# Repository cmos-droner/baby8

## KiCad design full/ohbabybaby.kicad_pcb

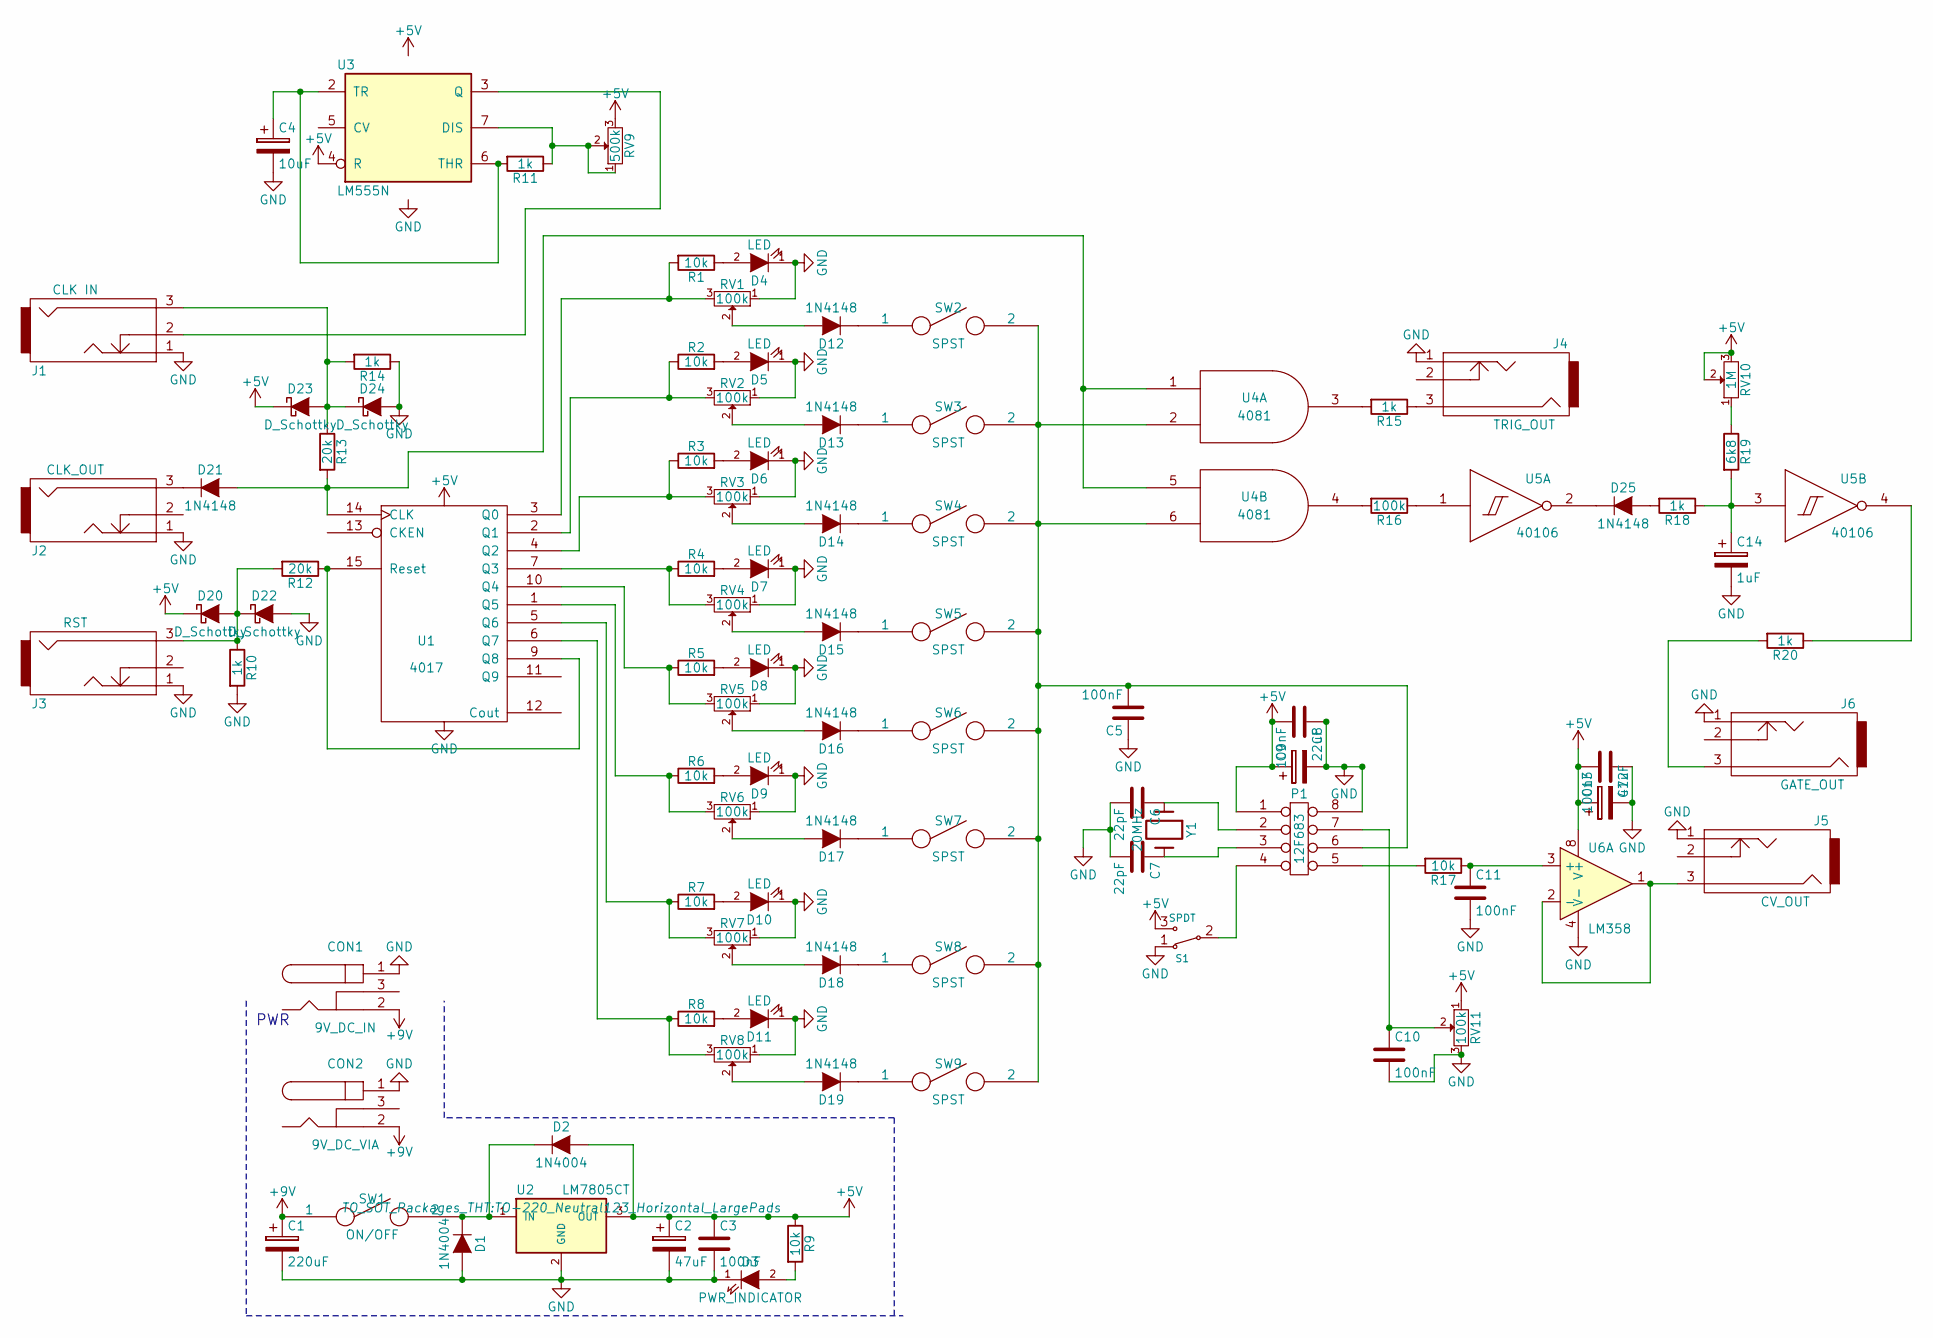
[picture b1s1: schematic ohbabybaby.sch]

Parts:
C1: 220uF; C_Radial_D8_L11.5_P3.5
C2, C13: 47uF; C_Radial_D7.5_L11.2_P2.5
C3, C5, C8, C10, C11, C12: 100nF; C_Rect_L7_W2.5_P5
C4: 10uF; C_Radial_D5_L11_P2.5
C6, C7: 22pF; C_Rect_L7_W2.5_P5
C9: 22uF; C_Radial_D5_L11_P2.5
C14: 1uF; C_Radial_D5_L11_P2.5
CON1: 9V_DC_IN; BARREL_JACK
CON2: 9V_DC_VIA; BARREL_JACK
D1, D2: 1N4004; Diode_DO-41_SOD81_Horizontal_RM10
D3: PWR_INDICATOR; LED-5MM-3
D4, D5, D6, D7, D8, D9, D10, D11: LED; LED-5MM-3
D12, D13, D14, D15, D16, D17, D18, D19, D21, D25: 1N4148; Diode_DO-35_SOD27_Horizontal_RM10
D20, D22, D23, D24: D_Schottky; Diode_DO-41_SOD81_Horizontal_RM10
J1: CLK IN; THONKICONN
J2: CLK_OUT; THONKICONN
J3: RST; THONKICONN
J4: TRIG_OUT; THONKICONN
J5: CV_OUT; THONKICONN
J6: GATE_OUT; THONKICONN
P1: 12F683; DIP-8_W7.62mm_LongPads
R1, R2, R3, R4, R5, R6, R7, R8, R9, R17: 10k; Resistor_Horizontal_RM7mm
R10, R11, R14, R15, R18, R20: 1k; Resistor_Horizontal_RM7mm
R12, R13: 20k; Resistor_Horizontal_RM7mm
R16: 100k; Resistor_Horizontal_RM7mm
R19: 6k8; Resistor_Horizontal_RM7mm
RV1, RV2, RV3, RV4, RV5, RV6, RV7, RV8, RV11: 100k; POT_ALPHA_9MM_V
RV9: 500k; POT_ALPHA_9MM_V
RV10: 1M; POT_ALPHA_9MM_V
S1: SPDT; SWITCH_SPDT
SW1: ON/OFF; SWITCH_SPDT_ANGLED_V
SW2, SW3, SW4, SW5, SW6, SW7, SW8, SW9: SPST; SWITCH_SPDT
U1: 4017; DIP-16_W7.62mm_LongPads
U2: LM7805CT; TO-220_Neutral123_Horizontal_LargePads
U3: LM555N; DIP-8_W7.62mm_LongPads
U4: 4081; DIP-14_W7.62mm_LongPads
U5: 40106; DIP-14_W7.62mm_LongPads
U6: LM358; DIP-8_W7.62mm_LongPads
Y1: 20MHz; Crystal_HC49-U_Vertical

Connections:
+5V: C2.1, C3.1, C8.2, C9.1, C12.2, C13.1, D2.2 (A), D20.1 (K), D23.1 (K), P1.1, R9.1, RV9.3, RV10.2, RV10.3, RV11.1, S1.3, U1.16 (VDD), U2.3 (OUT), U3.4 (R), U3.8 (VCC), U4.14 (VDD), U5.14 (VDD), U6.8 (V+)
+9V: C1.1, CON1.2, CON2.2, SW1.1
GND: C1.2, C2.2, C3.2, C4.2, C5.1, C6.2, C7.2, C8.1, C9.2, C10.2, C11.2, C12.1, C13.2, C14.2, CON1.1, CON2.1, D1.2 (A), D3.1 (K), D4.1 (K), D5.1 (K), D6.1 (K), D7.1 (K), D8.1 (K), D9.1 (K), D10.1 (K), D11.1 (K), D22.2 (A), D24.2 (A), J1.1, J2.1, J3.1, J4.1, J5.1, J6.1, P1.8, R10.2, R14.1, RV1.1, RV2.1, RV3.1, RV4.1, RV5.1, RV6.1, RV7.1, RV8.1, RV11.3, S1.1, U1.8 (VSS), U2.2 (GND), U3.1 (GND), U4.7 (VSS), U5.7 (VSS), U6.4 (V-)
unnamed: C4.1, R11.2, U3.2 (TR), U3.6 (THR)
unnamed: C5.2, P1.6, SW2.2, SW3.2, SW4.2, SW5.2, SW6.2, SW7.2, SW8.2, SW9.2, U4.2, U4.6
unnamed: C6.1, P1.2, Y1.1
unnamed: C7.1, P1.3, Y1.2
unnamed: C10.1, P1.7, RV11.2
unnamed: C11.1, R17.1, U6.3 (+)
unnamed: C14.1, R18.1, R19.2, U5.3 (In)
unnamed: D1.1 (K), D2.1 (K), SW1.2, U2.1 (IN)
unnamed: D3.2 (A), R9.2
unnamed: D4.2 (A), R1.1
unnamed: D5.2 (A), R2.2
unnamed: D6.2 (A), R3.2
unnamed: D7.2 (A), R4.2
unnamed: D8.2 (A), R5.2
unnamed: D9.2 (A), R6.2
unnamed: D10.2 (A), R7.2
unnamed: D11.2 (A), R8.2
unnamed: D12.1 (K), SW2.1
unnamed: D12.2 (A), RV1.2
unnamed: D13.1 (K), SW3.1
unnamed: D13.2 (A), RV2.2
unnamed: D14.1 (K), SW4.1
unnamed: D14.2 (A), RV3.2
unnamed: D15.1 (K), SW5.1
unnamed: D15.2 (A), RV4.2
unnamed: D16.1 (K), SW6.1
unnamed: D16.2 (A), RV5.2
unnamed: D17.1 (K), SW7.1
unnamed: D17.2 (A), RV6.2
unnamed: D18.1 (K), SW8.1
unnamed: D18.2 (A), RV7.2
unnamed: D19.1 (K), SW9.1
unnamed: D19.2 (A), RV8.2
unnamed: D20.2 (A), D22.1 (K), J3.3, R10.1, R12.2
unnamed: D21.1 (K), J2.3
unnamed: D21.2 (A), R13.2, U1.14 (CLK), U4.1, U4.5
unnamed: D23.2 (A), D24.1 (K), J1.3, R13.1, R14.2
unnamed: D25.1 (K), U5.2 (Out)
unnamed: D25.2 (A), R18.2
unnamed: J1.2, U3.3 (Q)
unnamed: J4.3, R15.1
unnamed: J5.3, U6.1, U6.2 (-)
unnamed: J6.3, R20.2
unnamed: P1.4, S1.2
unnamed: P1.5, R17.2
unnamed: R1.2, RV1.3, U1.3 (Q0)
unnamed: R2.1, RV2.3, U1.2 (Q1)
unnamed: R3.1, RV3.3, U1.4 (Q2)
unnamed: R4.1, RV4.3, U1.7 (Q3)
unnamed: R5.1, RV5.3, U1.10 (Q4)
unnamed: R6.1, RV6.3, U1.1 (Q5)
unnamed: R7.1, RV7.3, U1.5 (Q6)
unnamed: R8.1, RV8.3, U1.6 (Q7)
unnamed: R11.1, RV9.1, RV9.2, U3.7 (DIS)
unnamed: R12.1, U1.9 (Q8), U1.15 (Reset)
unnamed: R15.2, U4.3
unnamed: R16.1, U5.1 (In)
unnamed: R16.2, U4.4
unnamed: R19.1, RV10.1
unnamed: R20.1, U5.4 (Out)

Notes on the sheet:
PWR

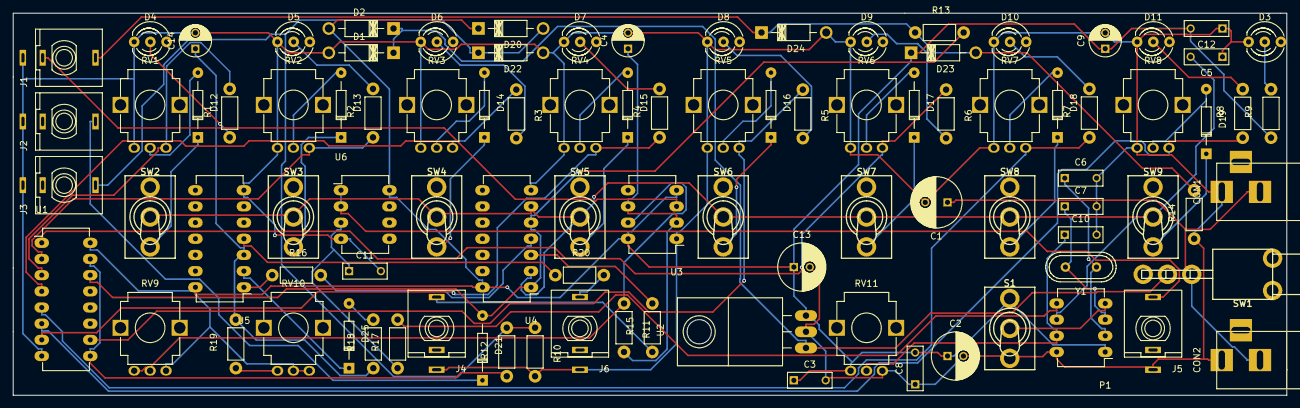
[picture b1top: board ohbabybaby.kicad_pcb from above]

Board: 2 copper layers, 200.0 x 60.0 mm, 96 parts (0 on the bottom side), 63 nets.
